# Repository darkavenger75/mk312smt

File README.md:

# mk-312 smt

## Introduction

A SMT version of the mk312-bt with several improvements

- More modern and efficient components in the power and output stage
- Input buttons more interference-proof to avoid the ATmega crashing
- And the best thing: someone like JLCPCB can do the assembly for you, you only need to add a few through-hole components and fit everything into the case. 

Main and control PCB are compatible with the THT versions, so that you can replace just one of them and keep the other PCB.

## Board ordering instructions 

PCB
- Default settings by JLCPCB work fine. Feel free to choose different color, etc. Lead-free recommended for the sake of the environment.

Assembly
- Economic, Bottom side (control PCB) / Top side (main PCB), as many PCBs as you wish. "Confirm Parts Placement" recommended. 
- Automatic selection of parts after uploading BOM and CPL worked well, but better check for obvious errors here and in part placement. 
- BOMs contain all components, including the THT ones. If you want to place the THT parts yourself just deselect them.

## Parts ordering information

You will in addition require
- Anything not on the PCB itself (button covers, knobs for pots, display + pin header).
- Any part your manufacturer did not have in stock. In case of JLCPCB this means especially the 42TU200 or 42TL004 transformers. Other parts missing you might pre-order to avoid additional effort. 
- 2x12P ribbon cable with connectors.
- A lead-acid battery of your choice. You can alternatively use a 12V LiFePO4 battery (with BMS), for that you need a matching charger (instead of the 15V power supply) and have to move the "jumper" (0R resistor) from "LDO" to "DIR" position to skip the voltage regulator. If you plan to use a LiFePO4 battery from the beginning (making the device much lighter) you can move the 0R resistor already when ordering and leave out V_REG (TPS73801), R1, R2, C2, C3, D1 from the beginning. These changes have been implemented in V2x which are now LiFePO4 only. 

## Board assembly Instructions

Nothing special here, just add the THT parts missing and mount the control panel to the front panel.

## Firmware

The firmware has not been modified, for instructions see the "firmware" folder. 

## Case

Fits in the stadard PACTEC case, see original BOM. 

## Update

- If the logic-level MOSFET IRLL2705 is not in stock at JLCPCB, it can be replaced by ZXMN4A06GTA or NDT3055L.
- The 5V DC-DC converter K7805MT-500R4 is no longer available. A version with a THT version has been added.
- If you like to keep using your 15V power supply with the LiFePO4 battery pack you can use V2b of the main PCB and the charger daughterboard.

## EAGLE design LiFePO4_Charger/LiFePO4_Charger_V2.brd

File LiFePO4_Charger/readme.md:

Daughterboard for the V2b main PCB.
LiFePO4 charger for the 4s battery pack so you can keep using your 15V power supply instead of using an external charger.

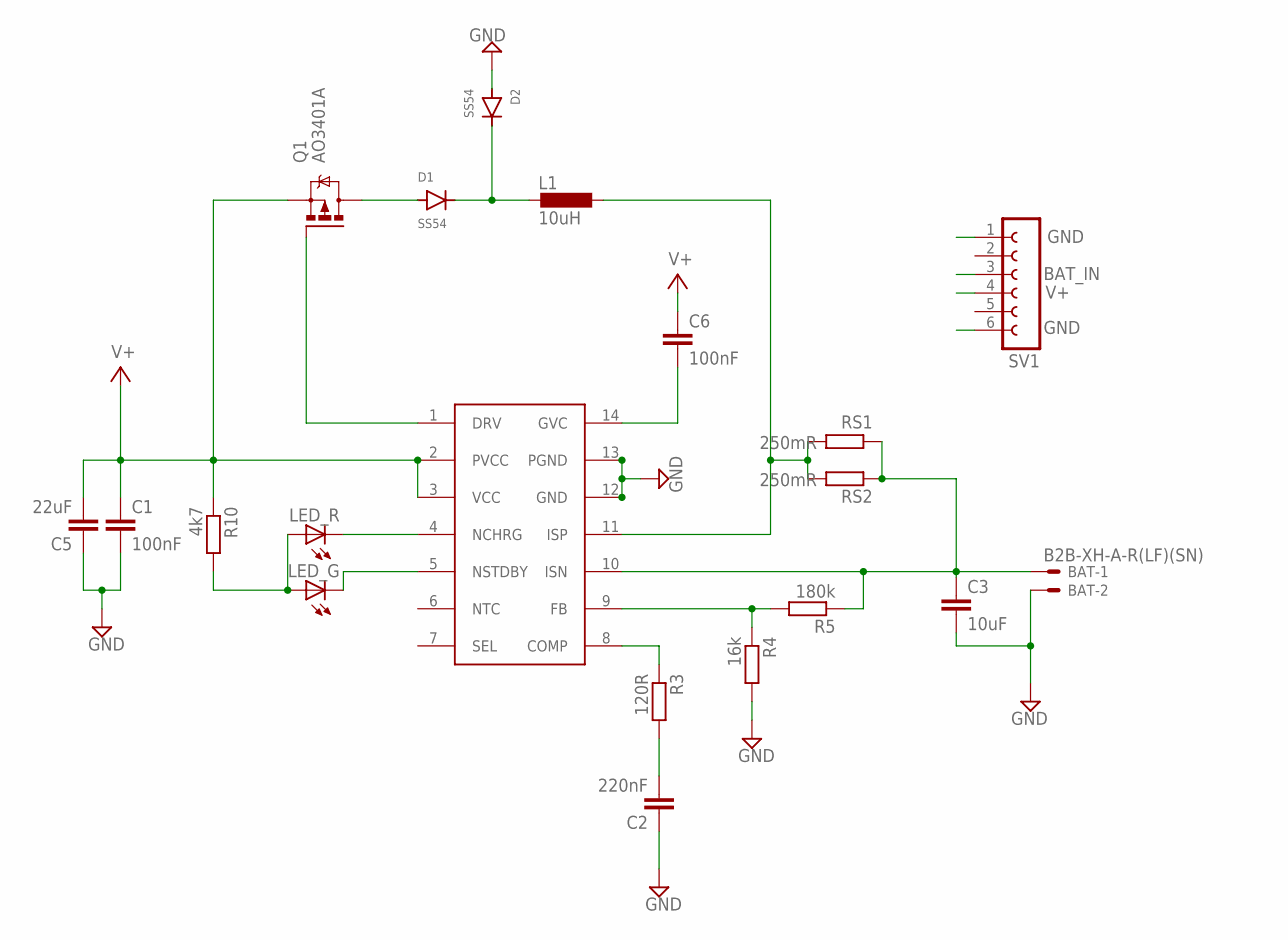
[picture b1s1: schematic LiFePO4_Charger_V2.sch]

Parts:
BAT: B2B-XH-A-R(LF)(SN); JST-XH-02-PACKAGE-LONG-PAD
C1, C6: 100nF; C0805
C2: 220nF; C0805
C3: 10uF; C0805
C5: 22uF; C0805
D1, D2: SS54; SMA
IC1: SLM6900; TSSOP14
L1: 10uH; FXL0630-100-M
LED_G: LEDCHIPLED_0805; CHIPLED_0805
LED_R: LEDCHIPLED_0805; CHIPLED_0805
Q1: AO3401A; MICRO3
R3: 120R; R0603
R4: 16k; R0805
R5: 180k; R0603
R10: 4k7; R0603
RS1, RS2: 250mR; R1206
SV1: FE06W

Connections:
BAT_IN: BAT.1, C3.1, IC1.10 (ISN), R5.1, RS1.1, RS2.1, SV1.3
GND: BAT.2, C1.2, C2.1, C3.2, C5.1, D2.A, IC1.12 (GND), IC1.13 (PGND), R4.2, SV1.1, SV1.6
unnamed: IC1.4 (NCHRG), LED_R.C
unnamed: IC1.5 (NSTDBY), LED_G.C
unnamed: LED_G.A, LED_R.A, R10.2
unnamed: C6.2, IC1.14 (GVC)
unnamed: IC1.8 (COMP), R3.1
unnamed: C2.2, R3.2
unnamed: D1.C, D2.C, L1.P$1 (1)
unnamed: IC1.9 (FB), R4.1, R5.2
unnamed: D1.A, Q1.3 (D)
unnamed: IC1.1 (DRV), Q1.1 (G)
unnamed: IC1.11 (ISP), L1.P$2 (2), RS1.2, RS2.2
V+: C1.1, C5.2, C6.1, IC1.2 (PVCC), IC1.3 (VCC), Q1.2 (S), R10.1, SV1.4

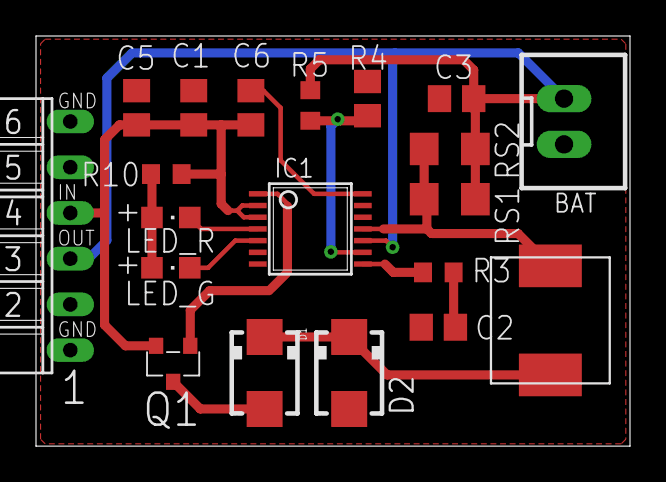
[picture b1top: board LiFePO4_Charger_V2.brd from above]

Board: 2 copper layers, 33.0 x 22.8 mm, 20 parts (0 on the bottom side), 14 nets.

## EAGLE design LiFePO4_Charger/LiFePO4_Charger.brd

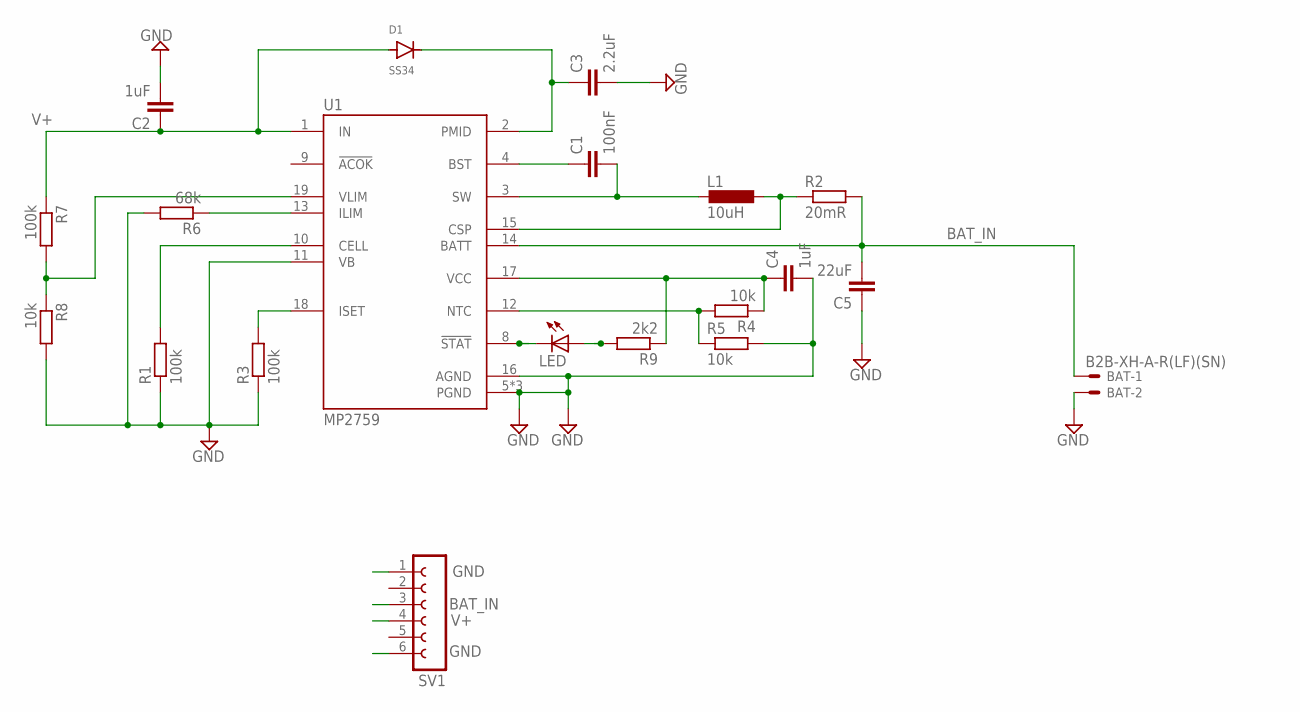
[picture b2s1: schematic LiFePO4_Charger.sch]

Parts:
BAT: B2B-XH-A-R(LF)(SN); JST-XH-02-PACKAGE-LONG-PAD
C1: 100nF; C0805
C2, C4: 1uF; C0805
C3: 2.2uF; C0805
C5: 22uF; C0805
D1: SS34; SMA
L1: 10uH; FXL0630-100-M
LED: LEDCHIPLED_0805; CHIPLED_0805
R1, R3, R7: 100k; R0603
R2: 20mR; R1206
R4, R5, R8: 10k; R0603
R6: 68k; R0603
R9: 2k2; R0603
SV1: FE06W
U1: MP2759; IC_MP2759GQ-0000-P

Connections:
BAT_IN: BAT.1, C5.2, R2.2, SV1.3, U1.14 (BATT)
BST: C1.1, U1.4 (BST)
GND: BAT.2, C2.2, C3.2, C4.2, C5.1, R1.1, R3.1, R5.2, R6.2, R8.2, SV1.1, SV1.6, U1.5 (PGND), U1.6 (PGND), U1.7 (PGND), U1.11 (VB), U1.16 (AGND)
unnamed: R1.2, U1.10 (CELL)
unnamed: C3.1, D1.C, U1.2 (PMID)
unnamed: L1.P$2 (2), R2.1, U1.15 (CSP)
unnamed: R3.2, U1.18 (ISET)
unnamed: R4.2, R5.1, U1.12 (NTC)
unnamed: R6.1, U1.13 (ILIM)
unnamed: LED.C, U1.8 (!STAT)
unnamed: R7.2, R8.1, U1.19 (VLIM)
unnamed: LED.A, R9.2
SW: C1.2, L1.P$1 (1), U1.3 (SW)
V+: C2.1, D1.A, R7.1, SV1.4, U1.1 (IN)
VCC: C4.1, R4.1, R9.1, U1.17 (VCC)

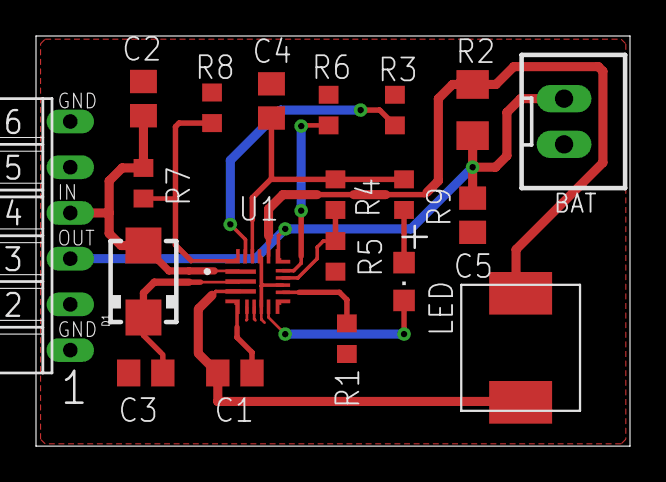
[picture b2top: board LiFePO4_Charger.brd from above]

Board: 2 copper layers, 33.0 x 22.8 mm, 20 parts (0 on the bottom side), 15 nets.

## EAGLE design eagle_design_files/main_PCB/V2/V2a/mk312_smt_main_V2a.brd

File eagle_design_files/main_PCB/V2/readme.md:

5V DC-DC converter replaced by PTH version because of much better availability.
Version 2a with lower cost connectors and power switch. Version 2b has a connector for the LiFePO4 charger daughterboard.

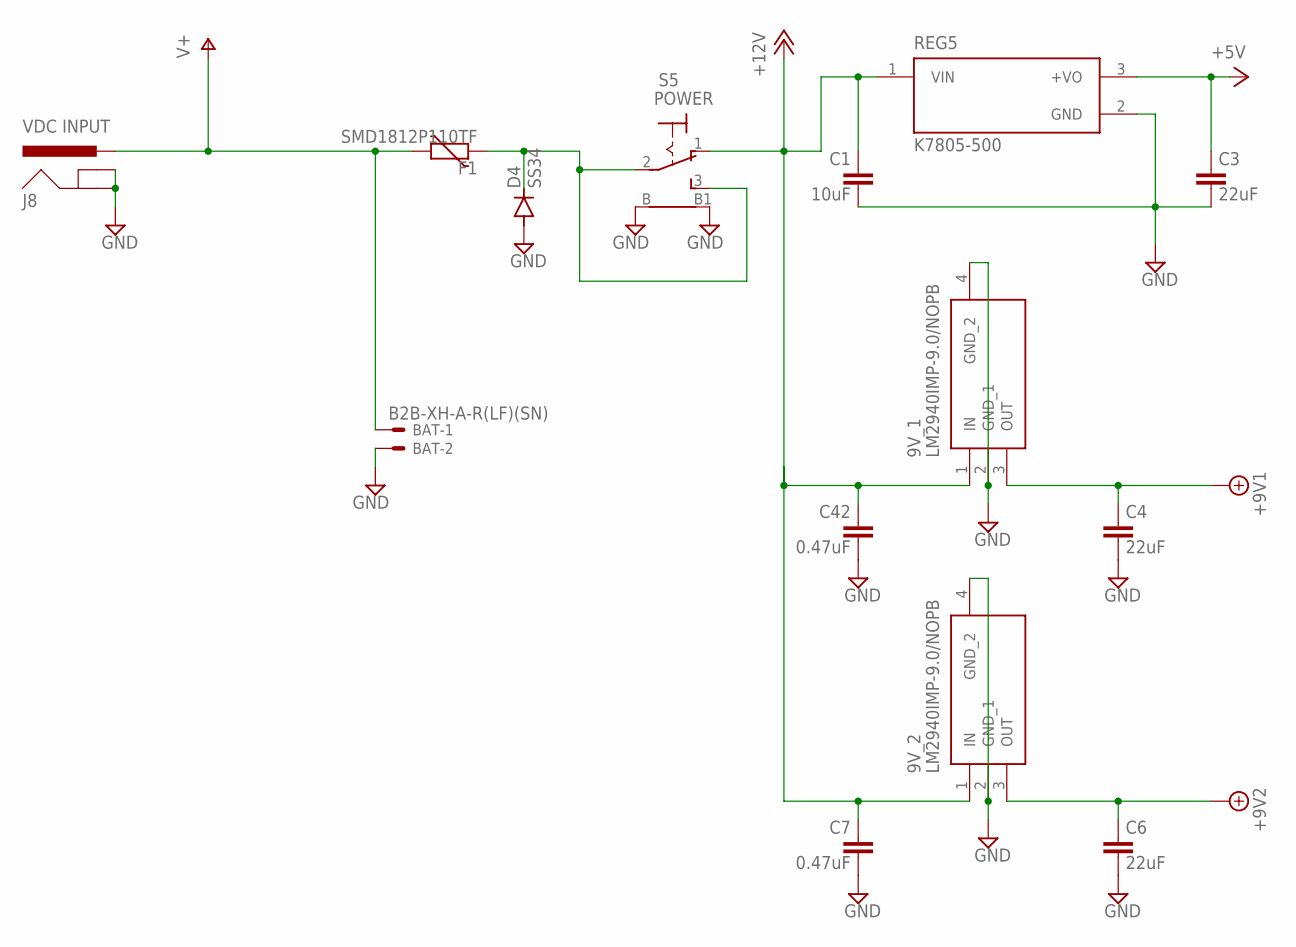
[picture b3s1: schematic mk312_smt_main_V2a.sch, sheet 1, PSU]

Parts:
9V_1, 9V_2: LM2940IMP-9.0/NOPB; SOT230P700X180-4N
BAT: B2B-XH-A-R(LF)(SN); JST-XH-02-PACKAGE-LONG-PAD
C1: 10uF; C0805
C3, C4, C6: 22uF; C1206
C7, C42: 0.47uF; C0805
D4: SS34; SMA
F1: SMD1812P110TF; CT/CN1812
J8: VDC INPUT; POWER_JACK_PTH_SLOT
REG5: K7805-500; CONV_K7809M-1000R3
S5: POWER; LPV-1

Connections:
+5V: C3.1, REG5.3 (+VO); also elsewhere on the board
+9V1: 9V_1.3 (OUT), C4.1; also elsewhere on the board
+9V2: 9V_2.3 (OUT), C6.1; also elsewhere on the board
+12V: 9V_1.1 (IN), 9V_2.1 (IN), C1.1, C7.1, C42.1, REG5.1 (VIN), S5.1 (O); also elsewhere on the board
GND: 9V_1.2 (GND_1), 9V_1.4 (GND_2), 9V_2.2 (GND_1), 9V_2.4 (GND_2), BAT.2, C1.2, C3.2, C4.2, C6.2, C7.2, C42.2, D4.A, J8.GND, J8.GNDBREAK, REG5.2 (GND), S5.B, S5.B1; also elsewhere on the board
unnamed: D4.C, F1.2, S5.2, S5.3 (S)
V+: BAT.1, F1.1, J8.PWR; also elsewhere on the board

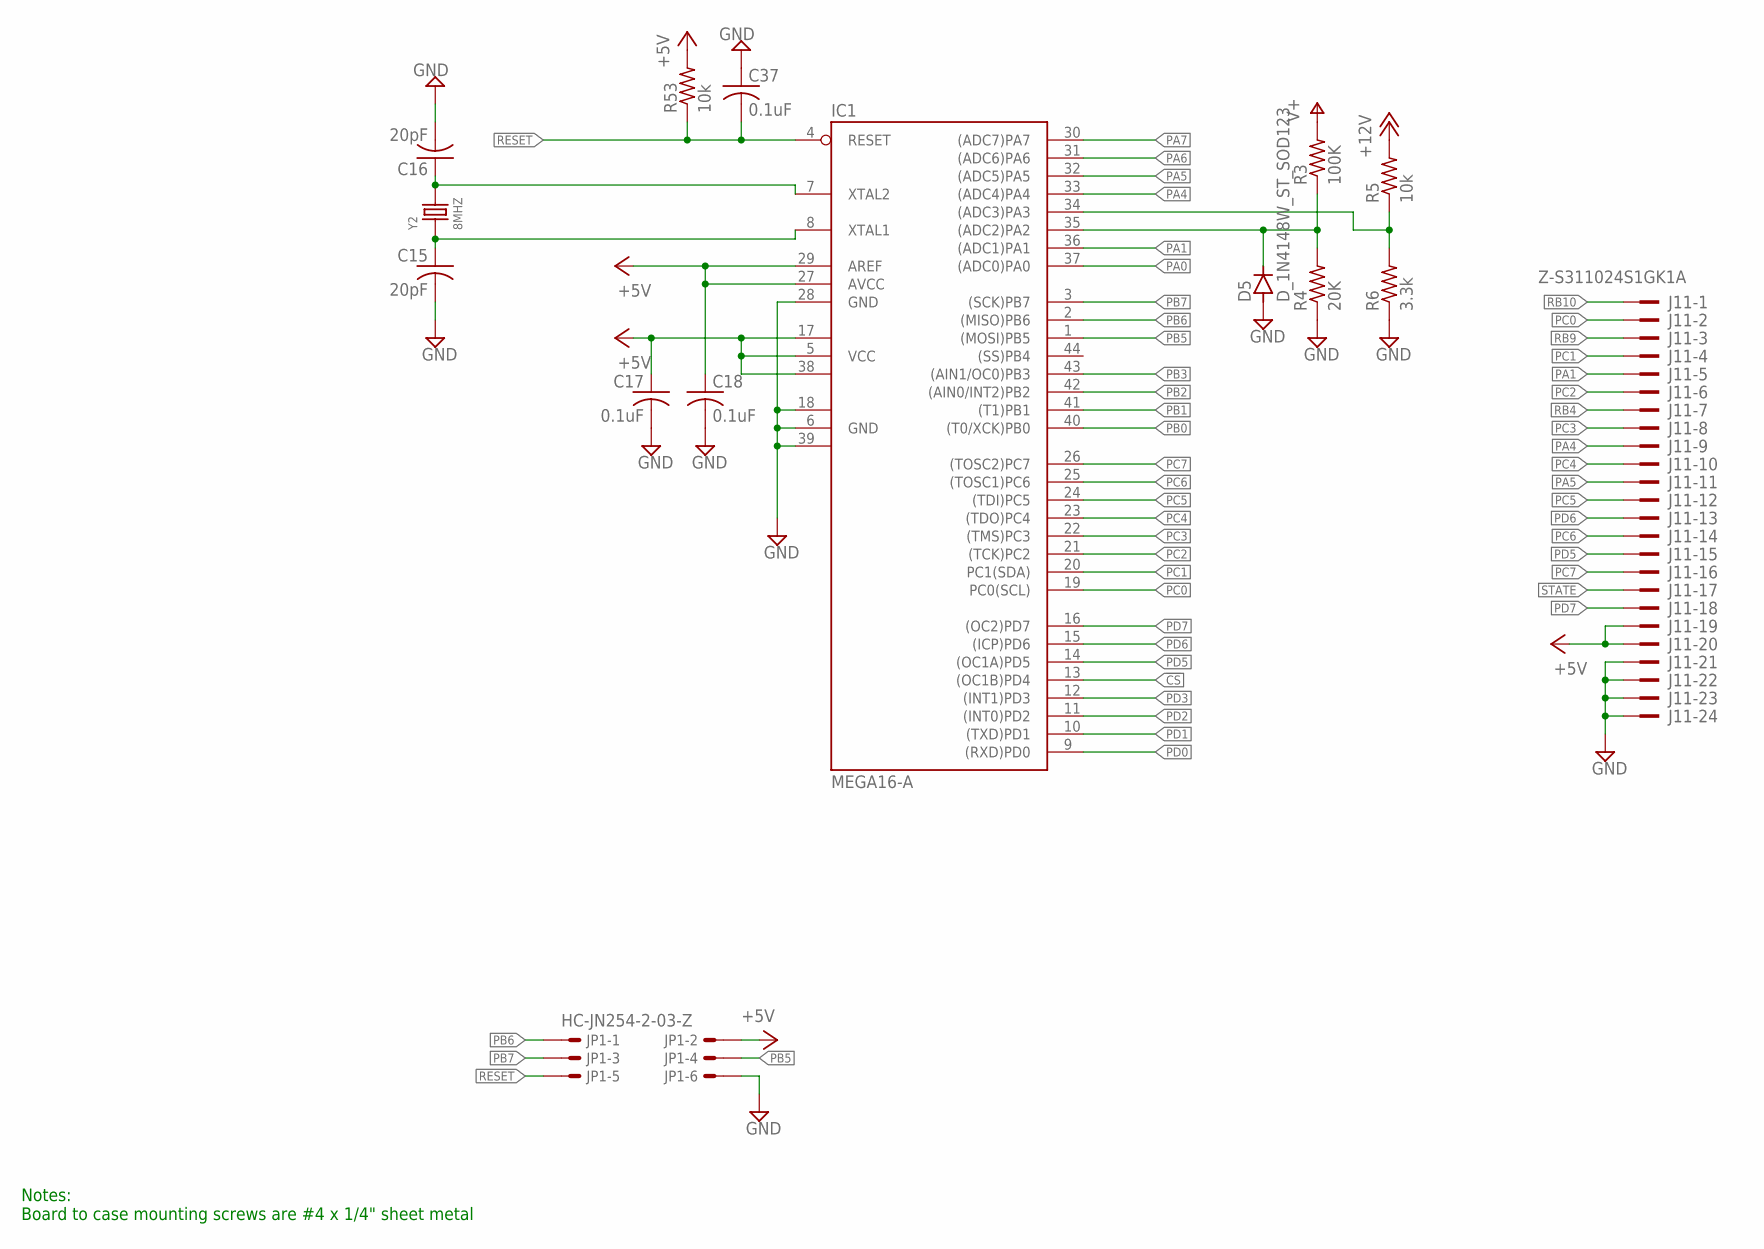
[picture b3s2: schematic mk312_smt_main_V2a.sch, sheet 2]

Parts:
C15, C16: 20pF; C0603
C17, C18, C37: 0.1uF; C0805
D5: D_1N4148W_ST_SOD123; SOD123
IC1: MEGA16-A; TQFP44
J11: Z-S311024S1GK1A; PAK100/2500-24
JP1: HC-JN254-2-03-Z; 057-006-1
R3: 100K; R0805
R4: 20K; R0805
R5, R53: 10k; R0805
R6: 3.3k; R0805
Y2: 8MHZ; X2-SMD-5.0X3.2X1.3MM

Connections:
!CS: IC1.13 ((OC1B)PD4); also elsewhere on the board
+5V: C17.1, C18.1, IC1.5 (VCC), IC1.17 (VCC1), IC1.27 (AVCC), IC1.29 (AREF), IC1.38 (VCC2), J11.19, J11.20, JP1.2, R53.2; also elsewhere on the board
+12V: R5.2; also elsewhere on the board
GND: C15.2, C16.2, C17.2, C18.2, C37.1, D5.A, IC1.6 (GND), IC1.18 (GND1), IC1.28 (GND), IC1.39 (GND2), J11.21, J11.22, J11.23, J11.24, JP1.6, R4.1, R6.1; also elsewhere on the board
unnamed: C16.1, IC1.7 (XTAL2), Y2.2
unnamed: IC1.34 ((ADC3)PA3), R5.1, R6.2
unnamed: D5.C, IC1.35 ((ADC2)PA2), R3.1, R4.2
unnamed: C15.1, IC1.8 (XTAL1), Y2.1
PA0: IC1.37 ((ADC0)PA0); also elsewhere on the board
PA1: IC1.36 ((ADC1)PA1), J11.5; also elsewhere on the board
PA4: IC1.33 ((ADC4)PA4), J11.9
PA5: IC1.32 ((ADC5)PA5), J11.11
PA6: IC1.31 ((ADC6)PA6); also elsewhere on the board
PA7: IC1.30 ((ADC7)PA7); also elsewhere on the board
PB0: IC1.40 ((T0/XCK)PB0); also elsewhere on the board
PB1: IC1.41 ((T1)PB1); also elsewhere on the board
PB2: IC1.42 ((AIN0/INT2)PB2); also elsewhere on the board
PB3: IC1.43 ((AIN1/OC0)PB3); also elsewhere on the board
PB5: IC1.1 ((MOSI)PB5), JP1.4; also elsewhere on the board
PB6: IC1.2 ((MISO)PB6), JP1.1
PB7: IC1.3 ((SCK)PB7), JP1.3; also elsewhere on the board
PC0: IC1.19 (PC0(SCL)), J11.2
PC1: IC1.20 (PC1(SDA)), J11.4
PC2: IC1.21 ((TCK)PC2), J11.6
PC3: IC1.22 ((TMS)PC3), J11.8
PC4: IC1.23 ((TDO)PC4), J11.10
PC5: IC1.24 ((TDI)PC5), J11.12
PC6: IC1.25 ((TOSC1)PC6), J11.14
PC7: IC1.26 ((TOSC2)PC7), J11.16
PD0: IC1.9 ((RXD)PD0); also elsewhere on the board
PD1: IC1.10 ((TXD)PD1); also elsewhere on the board
PD2: IC1.11 ((INT0)PD2); also elsewhere on the board
PD3: IC1.12 ((INT1)PD3); also elsewhere on the board
PD5: IC1.14 ((OC1A)PD5), J11.15
PD6: IC1.15 ((ICP)PD6), J11.13
PD7: IC1.16 ((OC2)PD7), J11.18
RB4: J11.7; also elsewhere on the board
RB9: J11.3; also elsewhere on the board
RB10: J11.1; also elsewhere on the board
RESET: C37.2, IC1.4 (RESET), JP1.5, R53.1
STATE: J11.17; also elsewhere on the board
V+: R3.2; also elsewhere on the board

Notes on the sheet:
Notes: Board to case mounting screws are #4 x 1/4" sheet metal

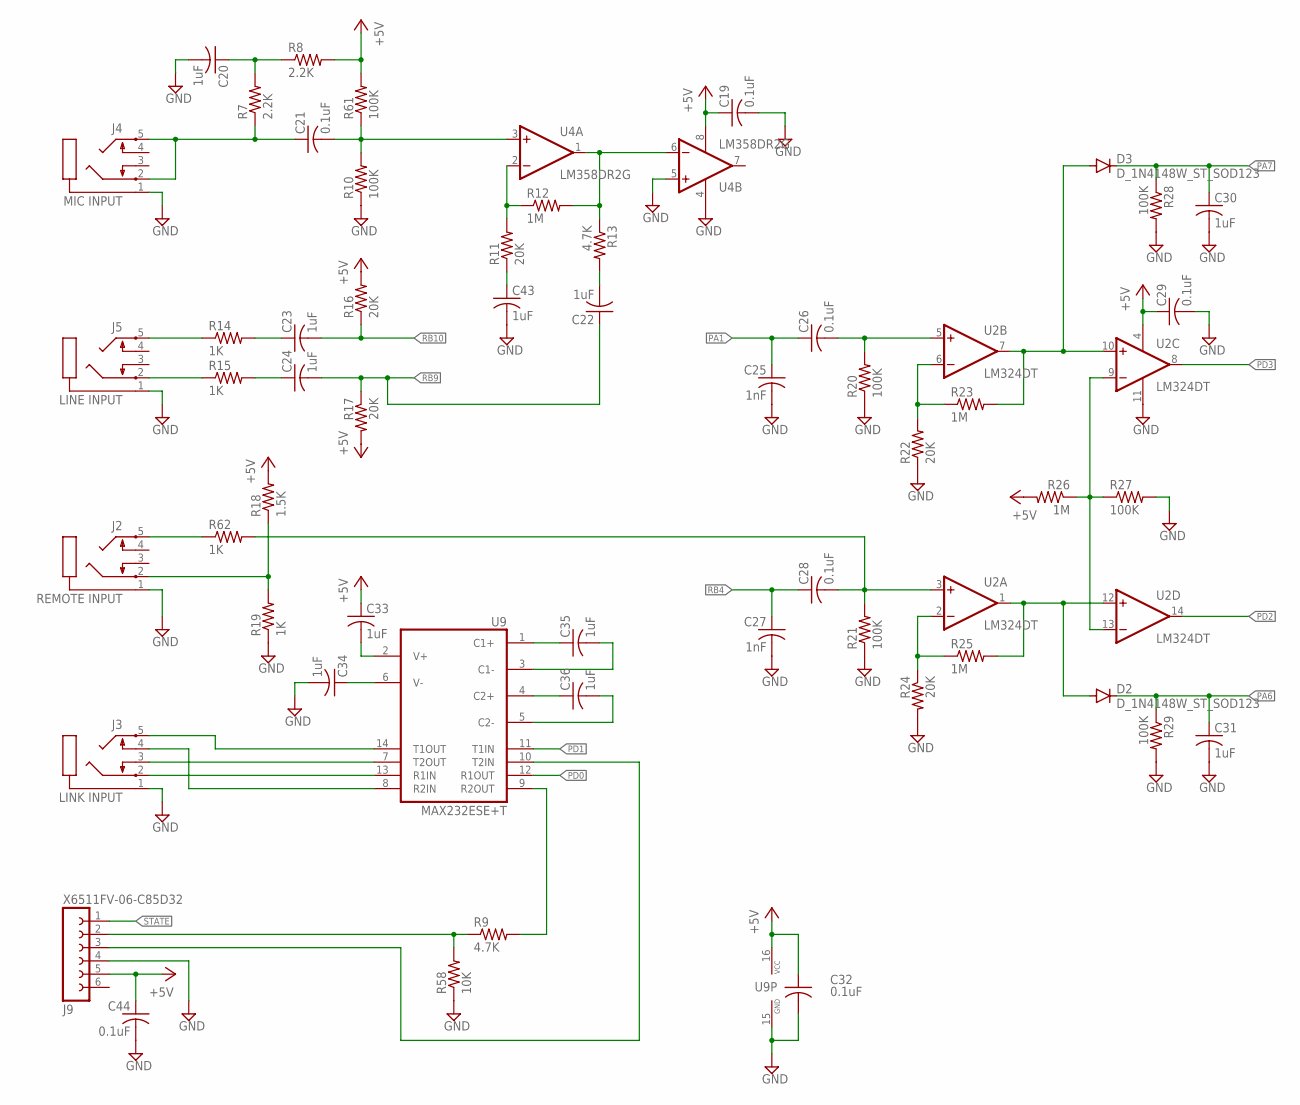
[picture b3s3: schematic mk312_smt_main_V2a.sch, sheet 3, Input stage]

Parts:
C19, C21, C26, C28, C29, C32, C44: 0.1uF; C0805
C20, C22, C23, C24, C30, C31, C33, C34, C35, C36, C43: 1uF; C0805
C25, C27: 1nF; C0805
D2, D3: D_1N4148W_ST_SOD123; SOD123
J2: REMOTE INPUT; PJ-3062
J3: LINK INPUT; PJ-3062
J4: MIC INPUT; PJ-3062
J5: LINE INPUT; PJ-3062
J9: X6511FV-06-C85D32; FE06
R7, R8: 2.2K; R0805
R9, R13: 4.7K; R0805
R10, R20, R21, R27, R28, R29, R61: 100K; R0805
R11, R16, R17, R22, R24: 20K; R0805
R12, R23, R25, R26: 1M; R0805
R14, R15, R19, R62: 1K; R0805
R18: 1.5K; R0805
R58: 10K; R0805
U2: LM324DT; SO14
U4: LM358DR2G; SO08
U9: MAX232ESE+T; SOP-16

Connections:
+5V: C19.1, C29.1, C32.1, C33.1, C44.1, J9.5, R8.2, R16.2, R17.2, R18.2, R26.2, R61.2, U2.4 (V+), U4.8 (V+), U9.16 (VCC); also elsewhere on the board
GND: C19.2, C20.2, C25.2, C27.2, C29.2, C30.2, C31.2, C32.2, C34.2, C43.2, C44.2, J2.1, J3.1, J4.1, J5.1, J9.4, R10.1, R19.1, R20.1, R21.1, R22.1, R24.2, R27.2, R28.2, R29.2, R58.1, U2.11 (V-), U4.4 (V-), U4.5 (+IN), U9.15 (GND); also elsewhere on the board
unnamed: C28.2, R21.2, R62.2, U2.3 (+IN)
unnamed: R9.2, U9.9 (R2OUT)
unnamed: J3.5, U9.14 (T1OUT)
unnamed: J3.2, U9.13 (R1IN)
unnamed: C43.1, R11.1
unnamed: J2.5, R62.1
unnamed: C35.1, U9.1 (C1+)
unnamed: R24.1, R25.1, U2.2 (-IN)
unnamed: D2.A, R25.2, U2.1 (OUT), U2.12 (+IN)
unnamed: J5.2, R15.1
unnamed: J5.5, R14.1
unnamed: C23.1, R14.2
unnamed: J2.2, R18.1, R19.2
unnamed: R22.2, R23.1, U2.6 (-IN)
unnamed: C35.2, U9.3 (C1-)
unnamed: R26.1, R27.1, U2.9 (-IN), U2.13 (-IN)
unnamed: C26.2, R20.2, U2.5 (+IN)
unnamed: C24.1, R15.2
unnamed: C36.2, U9.5 (C2-)
unnamed: C36.1, U9.4 (C2+)
unnamed: J9.2, R9.1, R58.2
unnamed: D3.A, R23.2, U2.7 (OUT), U2.10 (+IN)
unnamed: C34.1, U9.6 (V-)
unnamed: C21.1, J4.2, J4.5, R7.1
unnamed: C20.1, R7.2, R8.1
unnamed: C21.2, R10.2, R61.1, U4.3 (+IN)
unnamed: R11.2, R12.1, U4.2 (-IN)
unnamed: R12.2, R13.1, U4.1 (OUT), U4.6 (-IN)
unnamed: C22.2, R13.2
unnamed: C33.2, U9.2 (V+)
unnamed: J3.4, U9.8 (R2IN)
unnamed: J3.3, U9.7 (T2OUT)
unnamed: J9.3, U9.10 (T2IN)
PA1: C25.1, C26.1; also elsewhere on the board
PA6: C31.1, D2.C, R29.1; also elsewhere on the board
PA7: C30.1, D3.C, R28.1; also elsewhere on the board
PD0: U9.12 (R1OUT); also elsewhere on the board
PD1: U9.11 (T1IN); also elsewhere on the board
PD2: U2.14 (OUT); also elsewhere on the board
PD3: U2.8 (OUT); also elsewhere on the board
RB4: C27.1, C28.1; also elsewhere on the board
RB9: C22.1, C24.2, R17.1; also elsewhere on the board
RB10: C23.2, R16.1; also elsewhere on the board
STATE: J9.1; also elsewhere on the board

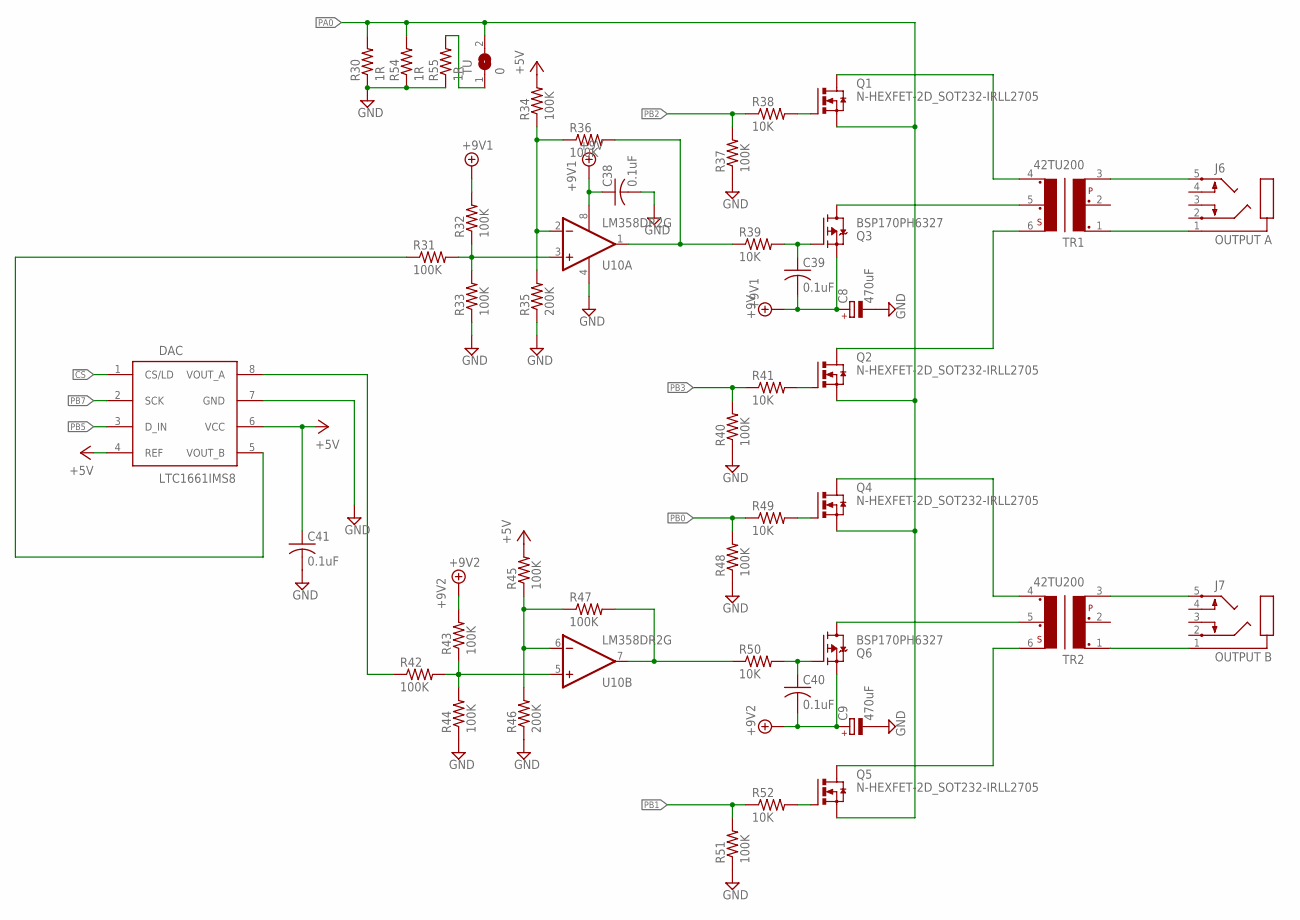
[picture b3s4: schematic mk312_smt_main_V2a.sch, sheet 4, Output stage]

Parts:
C8, C9: 470uF; 150CLZ-1010
C38, C39, C40, C41: 0.1uF; C0805
DAC: LTC1661IMS8; MSOP8
J6: OUTPUT A; PJ-3062
J7: OUTPUT B; PJ-3062
Q1, Q2, Q4, Q5: N-HEXFET-2D_SOT232-IRLL2705; SOT223
Q3, Q6: BSP170PH6327; SOT230P700X180-4N
R30, R54, R55: 1R; R1206
R31, R32, R33, R34, R36, R37, R40, R42, R43, R44, R45, R47, R48, R51: 100K; R0805
R35, R46: 200K; R0805
R38, R39, R41, R49, R50, R52: 10K; R0805
TR1, TR2: 42TU200; 42TL
TU: 0; SJ
U10: LM358DR2G; SO08

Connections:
!CS: DAC.1 (CS/LD); also elsewhere on the board
+5V: C41.1, DAC.4 (REF), DAC.6 (VCC), R34.2, R45.2; also elsewhere on the board
+9V1: C8.+, C38.1, C39.2, Q3.3 (S), R32.2, U10.8 (V+); also elsewhere on the board
+9V2: C9.+, C40.2, Q6.3 (S), R43.2; also elsewhere on the board
GND: C8.-, C9.-, C38.2, C41.2, DAC.7 (GND), R30.1, R33.1, R35.1, R37.1, R40.1, R44.1, R46.1, R48.1, R51.1, R54.1, R55.1, U10.4 (V-); also elsewhere on the board
unnamed: R55.2, TU.1
unnamed: Q3.2 (D), Q3.4 (D), TR1.5
unnamed: Q6.2 (D), Q6.4 (D), TR2.5
unnamed: J6.1, TR1.1
unnamed: Q1.1 (G), R38.2
unnamed: Q2.1 (G), R41.2
unnamed: C39.1, Q3.1 (G), R39.2
unnamed: R31.2, R32.1, R33.2, U10.3 (+IN)
unnamed: Q4.1 (G), R49.2
unnamed: Q5.1 (G), R52.2
unnamed: J7.1, TR2.1
unnamed: C40.1, Q6.1 (G), R50.2
unnamed: R42.2, R43.1, R44.2, U10.5 (+IN)
unnamed: Q1.2 (D), Q1.4 (D), TR1.4
unnamed: J6.5, TR1.3
unnamed: Q4.2 (D), Q4.4 (D), TR2.4
unnamed: J7.5, TR2.3
unnamed: Q5.2 (D), Q5.4 (D), TR2.6
unnamed: Q2.2 (D), Q2.4 (D), TR1.6
unnamed: R34.1, R35.2, R36.1, U10.2 (-IN)
unnamed: R45.1, R46.2, R47.1, U10.6 (-IN)
unnamed: DAC.5 (VOUT_B), R31.1
unnamed: DAC.8 (VOUT_A), R42.1
PA0: Q1.3 (S), Q2.3 (S), Q4.3 (S), Q5.3 (S), R30.2, R54.2, TU.2; also elsewhere on the board
PB0: R48.2, R49.1; also elsewhere on the board
PB1: R51.2, R52.1; also elsewhere on the board
PB2: R37.2, R38.1; also elsewhere on the board
PB3: R40.2, R41.1; also elsewhere on the board
PB5: DAC.3 (D_IN); also elsewhere on the board
PB7: DAC.2 (SCK); also elsewhere on the board
PFET_A: R36.2, R39.1, U10.1 (OUT)
PFET_B: R47.2, R50.1, U10.7 (OUT)

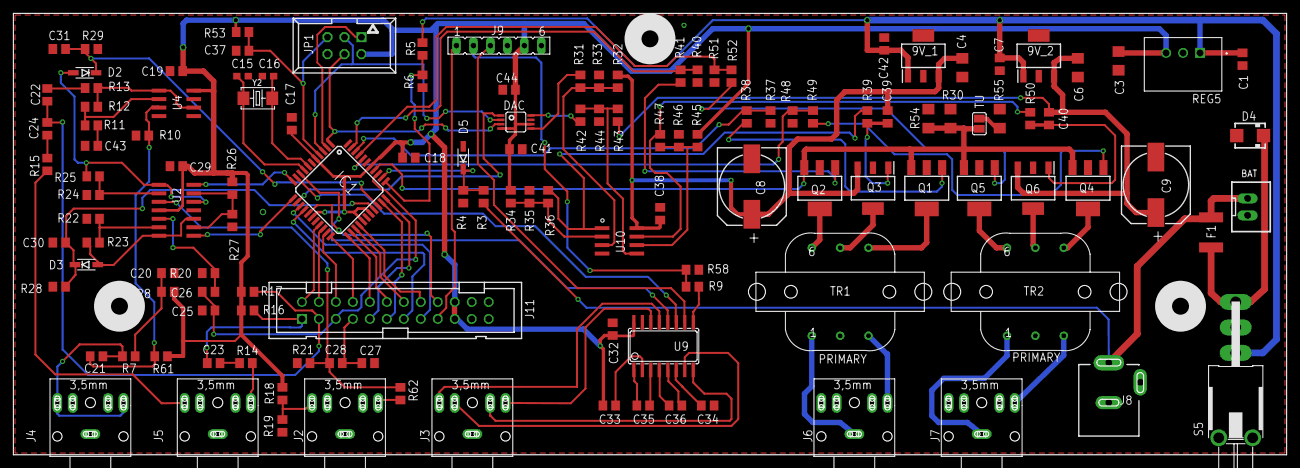
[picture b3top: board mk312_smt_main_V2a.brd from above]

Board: 2 copper layers, 190.5 x 66.0 mm, 129 parts (0 on the bottom side), 103 nets.

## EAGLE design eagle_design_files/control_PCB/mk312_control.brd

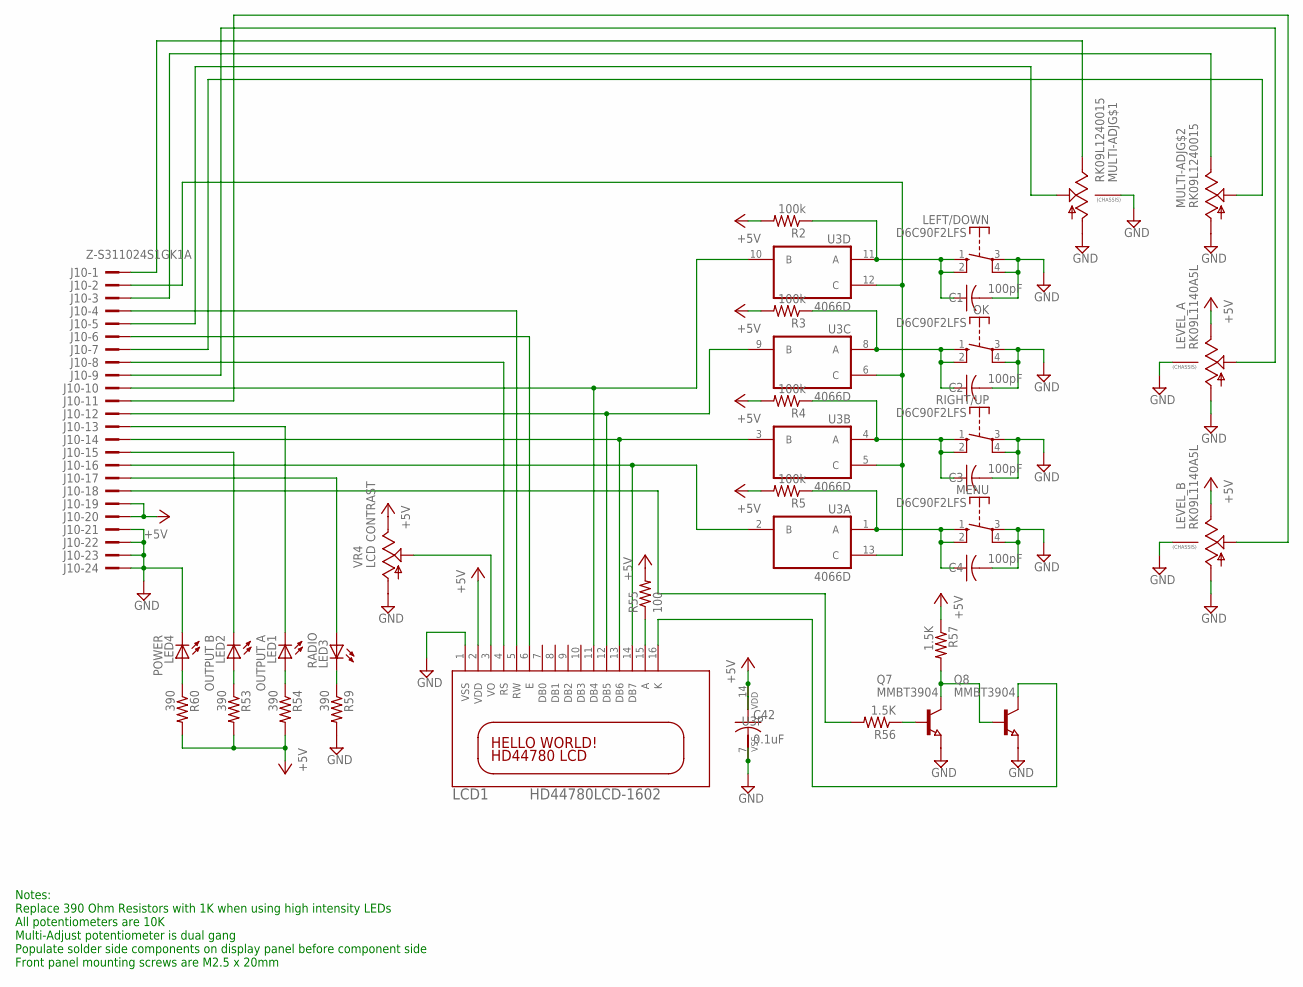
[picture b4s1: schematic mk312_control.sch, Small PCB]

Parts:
C1, C2, C3, C4: 100pF; C0805
C42: 0.1uF; C0805
J10: Z-S311024S1GK1A; PAK100/2500-24
LCD1: HD44780LCD-1602; LCD1602
LED1: OUTPUT A; LED5MM
LED2: OUTPUT B; LED5MM
LED3: RADIO; LED5MM
LED4: POWER; LED5MM
LEFT/DOWN: D6C90F2LFS; DTE6K
LEVEL_A: RK09L1140A5L; 9MM_SNAP-IN_POT
LEVEL_B: RK09L1140A5L; 9MM_SNAP-IN_POT
MENU: D6C90F2LFS; DTE6K
MULTI-ADJ: RK09L1240015; DUAL_9MM_SNAP-IN_POT
OK: D6C90F2LFS; DTE6K
Q7, Q8: MMBT3904; SOT23
R2, R3, R4, R5: 100k; R0805
R53, R54, R59, R60: 390; R0805
R55: 100; R0805
R56, R57: 1.5K; R0805
RIGHT/UP: D6C90F2LFS; DTE6K
U3: 4066D; SO14
VR4: LCD CONTRAST; B25P

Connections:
+5V: C42.1, J10.19, J10.20, LCD1.2 (VDD), LEVEL_A.3 (E), LEVEL_B.3 (E), R2.2, R3.2, R4.2, R5.2, R53.2, R54.2, R55.2, R57.1, R60.2, U3.14 (VDD), VR4.E
GND: C1.2, C2.2, C3.2, C4.2, C42.2, J10.21, J10.22, J10.23, J10.24, LCD1.1 (VSS), LED4.K (C), LEFT/DOWN.3, LEFT/DOWN.4, LEVEL_A.1 (A), LEVEL_A.CHASSIS2, LEVEL_B.1 (A), LEVEL_B.CHASSIS2, MENU.3, MENU.4, MULTI-ADJ.1 (A), MULTI-ADJ.1B (A), MULTI-ADJ.CHASSIS1, MULTI-ADJ.CHASSIS2, OK.3, OK.4, Q7.2 (E), Q8.2 (E), R59.2, RIGHT/UP.3, RIGHT/UP.4, U3.7 (VSS), VR4.A
unnamed: J10.7, MULTI-ADJ.2B (S)
unnamed: C2.1, OK.1 (S), OK.2 (S), R3.1, U3.8 (A)
unnamed: C1.1, LEFT/DOWN.1 (S), LEFT/DOWN.2 (S), R2.1, U3.11 (A)
unnamed: C3.1, R4.1, RIGHT/UP.1 (S), RIGHT/UP.2 (S), U3.4 (A)
unnamed: J10.3, MULTI-ADJ.3B (E)
unnamed: J10.9, LEVEL_A.2 (S)
unnamed: J10.11, LEVEL_B.2 (S)
unnamed: J10.1, MULTI-ADJ.3 (E)
unnamed: J10.5, MULTI-ADJ.2 (S)
unnamed: LED2.A, R53.1
unnamed: LED1.A, R54.1
unnamed: LCD1.3 (VO), VR4.S
unnamed: LCD1.15 (A), R55.1
unnamed: LED3.K (C), R59.1
unnamed: C4.1, MENU.1 (S), MENU.2 (S), R5.1, U3.1 (A)
unnamed: LED4.A, R60.1
unnamed: Q7.1 (B), R56.1
unnamed: Q7.3 (C), Q8.1 (B), R57.2
unnamed: LCD1.16 (K), Q8.3 (C)
unnamed: J10.17, LED3.A
PC0: J10.2, U3.5 (C), U3.6 (C), U3.12 (C), U3.13 (C)
PC1: J10.4, LCD1.5 (RW)
PC2: J10.6, LCD1.6 (E)
PC3: J10.8, LCD1.4 (RS)
PC4: J10.10, LCD1.11 (DB4), U3.10 (B)
PC5: J10.12, LCD1.12 (DB5), U3.9 (B)
PC6: J10.14, LCD1.13 (DB6), U3.3 (B)
PC7: J10.16, LCD1.14 (DB7), U3.2 (B)
PD5: J10.15, LED2.K (C)
PD6: J10.13, LED1.K (C)
PD7: J10.18, R56.2

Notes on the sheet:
Notes: Replace 390 Ohm Resistors with 1K when using high intensity LEDs All potentiometers are 10K Multi-Adjust potentiometer is dual gang Populate solder side components on display panel before component side Front panel mounting screws are M2.5 x 20mm

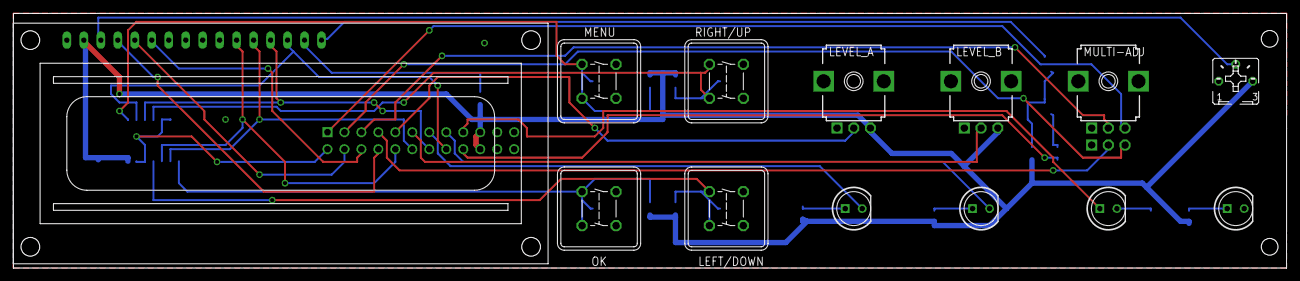
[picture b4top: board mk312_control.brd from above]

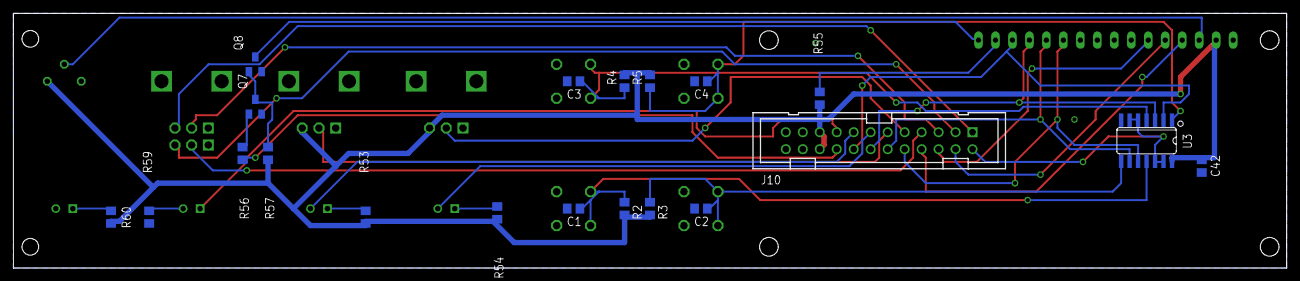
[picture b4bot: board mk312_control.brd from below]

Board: 2 copper layers, 190.5 x 38.1 mm, 33 parts (20 on the bottom side), 33 nets.

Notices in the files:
parts and their libraries:
SparkFun-Connectors: Licensing: Creative Commons ShareAlike 4.0 International - https://creativecommons.org/licenses/by-sa/4.0
